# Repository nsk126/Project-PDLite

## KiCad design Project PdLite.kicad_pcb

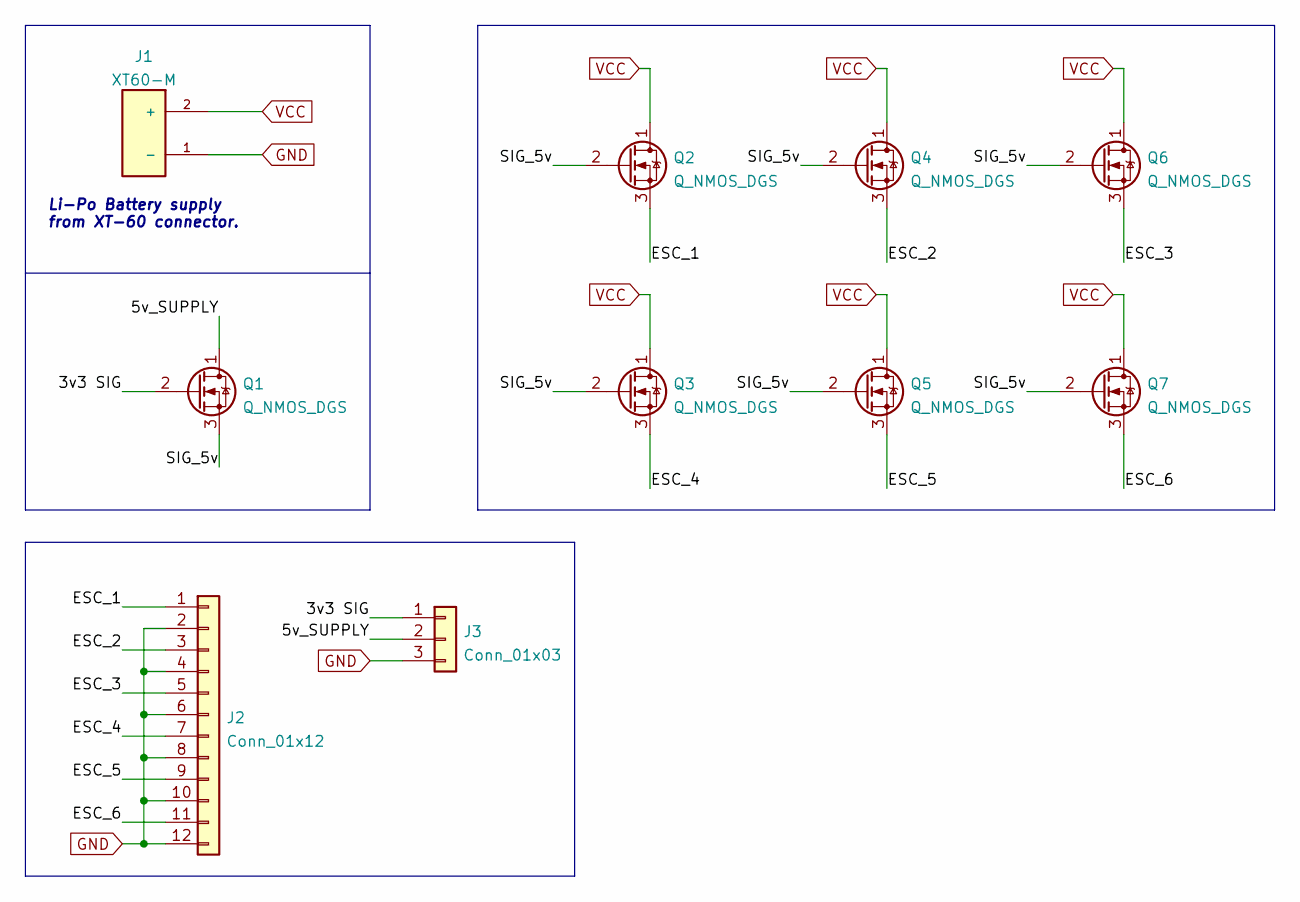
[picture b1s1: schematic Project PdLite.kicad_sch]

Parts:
J1: XT60-M; AMASS_XT60-M; PARTREV 1.2
J2: Conn_01x12; PinHeader_1x12_P1.27mm_Horizontal
J3: Conn_01x03; PinHeader_1x03_P1.27mm_Vertical
Q1: Q_NMOS_DGS; SOT-323_SC-70
Q2, Q3, Q4, Q5, Q6, Q7: Q_NMOS_DGS; TO-263-2

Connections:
/3v3 SIG: J3.1, Q1.2 (G)
/5v_SUPPLY: J3.2, Q1.1 (D)
/ESC_1: J2.1, Q2.3 (S)
/ESC_2: J2.3, Q4.3 (S)
/ESC_3: J2.5, Q6.3 (S)
/ESC_4: J2.7, Q3.3 (S)
/ESC_5: J2.9, Q5.3 (S)
/ESC_6: J2.11, Q7.3 (S)
/SIG_5v: Q1.3 (S), Q2.2 (G), Q3.2 (G), Q4.2 (G), Q5.2 (G), Q6.2 (G), Q7.2 (G)
GND: J1.1 (-), J2.2, J2.4, J2.6, J2.8, J2.10, J2.12, J3.3
VCC: J1.2 (+), Q2.1 (D), Q3.1 (D), Q4.1 (D), Q5.1 (D), Q6.1 (D), Q7.1 (D)

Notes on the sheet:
Li-Po Battery supply from XT-60 connector.

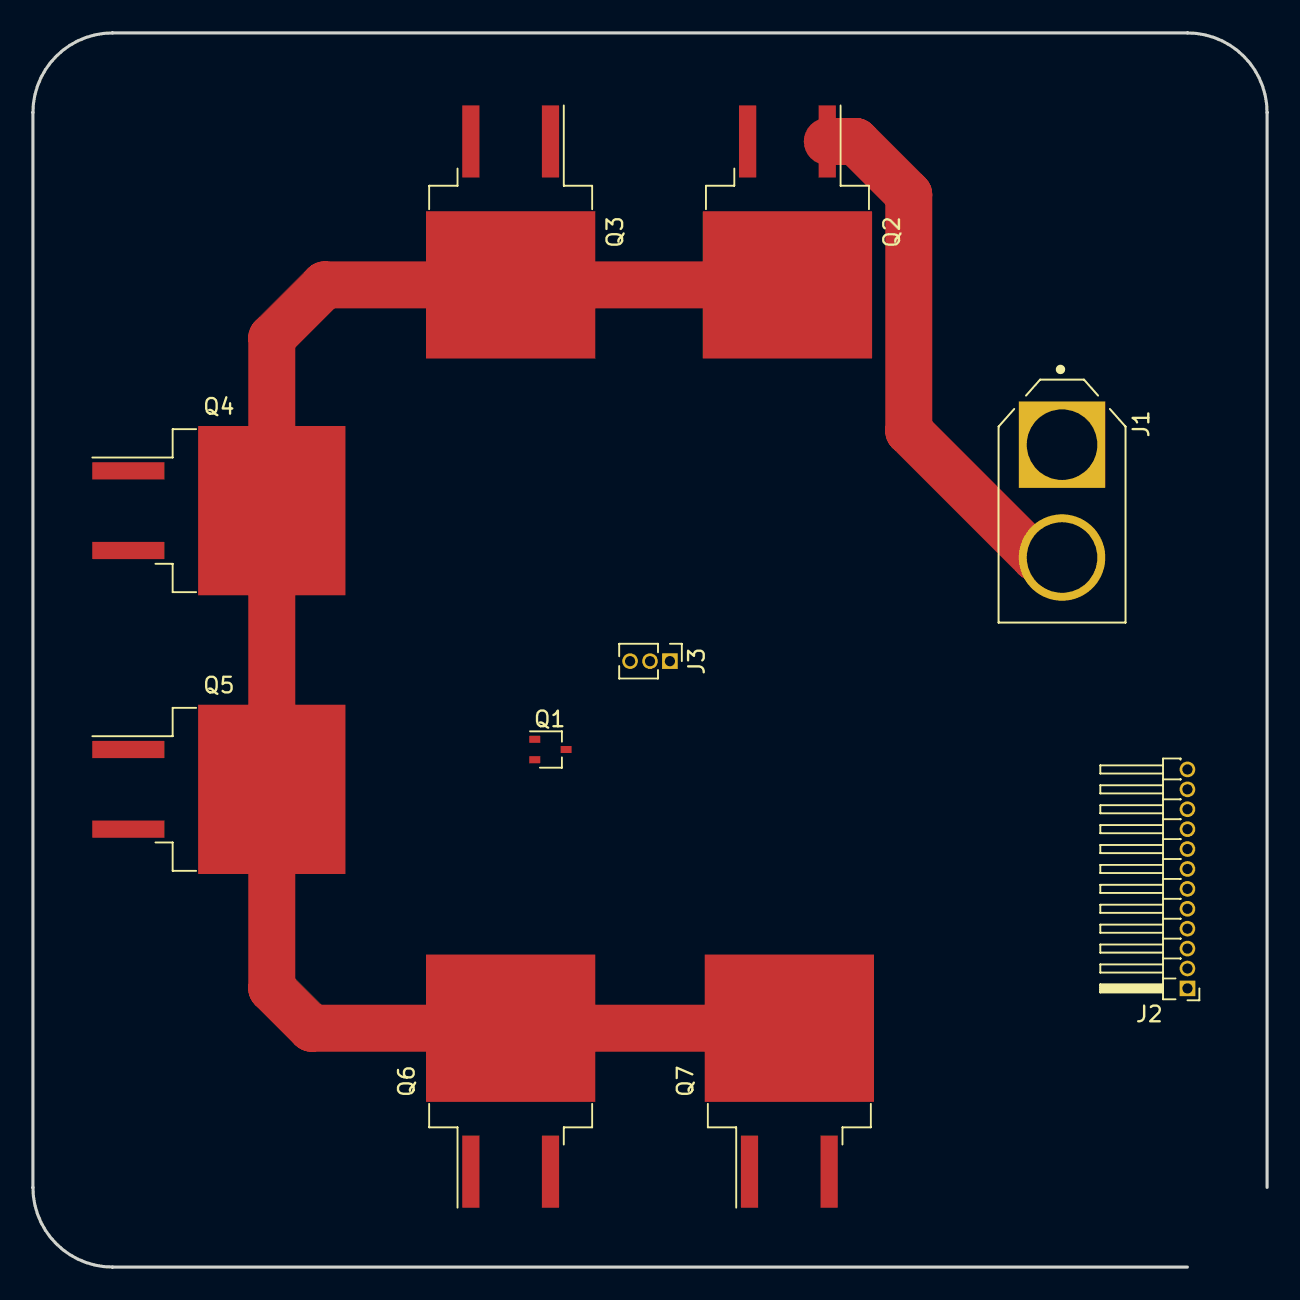
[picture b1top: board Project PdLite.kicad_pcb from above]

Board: 2 copper layers, 78.7 x 78.7 mm, 10 parts (0 on the bottom side), 11 nets.

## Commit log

2022-02-03 Project INIT
2022-02-03 added src folder
2022-02-03 added symbols and started sch
2022-02-03 fixed bugs added gen sch pcb
